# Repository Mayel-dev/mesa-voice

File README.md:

# Mesa Voice R1

Asistente de voz de sobremesa con botón para hablar, micrófono PDM, Wi-Fi, altavoz de 8 Ω y alimentación USB-C. Se conecta a un servidor Python local con faster-whisper, Ollama y Piper. El modo mock devuelve un tono para comprobar el transporte.

**Estado: entrega digital para un primer prototipo experimental, aún no construido.** La portadora pasa ERC y DRC con paridad esquema/PCB, sin conexiones pendientes. El firmware completo compila y enlaza para ESP32-S3; el backend pasa 41 pruebas y una petición HTTP real en localhost. Los tres STL son mallas cerradas y pasan la comprobación de interferencias nominales modeladas. No se ejecutó inferencia con modelos reales ni se probaron componentes físicos. Leer el [informe de validación](docs/validation.md) antes de fabricar.

## Entregables

| Carpeta / archivo | Contenido |
|---|---|
| `hardware/mesa-voice.kicad_pro` | Proyecto KiCad 9.0.6, esquema y PCB portadora propia de 64×54 mm, dos capas |
| `hardware/wiring.kicad_pro`, `wiring.kicad_sch` | Proyecto independiente de cableados del botón, LED y altavoz; seis conexiones verificadas |
| `hardware/Mesa.pretty`, bibliotecas `.kicad_sym` | Huellas y símbolos locales incluidos |
| `hardware/fabrication/` | Gerber X2, perforación PTH/NPTH, mapas, IPC-2581 y manifiesto con hashes |
| `hardware/mesa-voice-r1-fabrication.zip` | Paquete de fabricación generado sólo después de pasar comprobaciones |
| `hardware/previews/` | Vistas SVG y PNG del esquema, cobre y montaje |
| `hardware/references/` | Esquemas de los módulos de fabricante y atribución |
| `mechanical/` | CAD paramétrico OpenSCAD, tres STL y vistas de inspección |
| `firmware/` | Código ESP32-S3, configuración PlatformIO y pruebas C++ del protocolo |
| `backend/` | Servidor Python ejecutable, adaptadores locales y tests |
| `BOM.csv` | Lista consolidada con cantidades, referencias y especificaciones |
| `docs/` | Arquitectura, ensamblaje, mecánica, firmware, protocolo y validación |
| `validation/` | Informes originales, logs y plantilla para pruebas físicas |
| `tools/` | Generadores y verificaciones reproducibles |

La placa integra mediante zócalos un **Seeed XIAO ESP32S3 Sense 113991115** y un **Adafruit MAX98357A 3006**. Es una portadora personalizada, no un rediseño de sus circuitos RF/USB/MEMS internos. Usa cámara retirada y expansión Sense conectada. Caja cerrada 94×82×42 mm. No tiene wake word ni cancelación de eco.

## Probar el servidor sin hardware ni modelos

Python 3.12; desde `backend/`:

```powershell
python -m venv .venv
.\.venv\Scripts\Activate.ps1
python -m pip install -r requirements-dev.txt
python -m pytest -q
$env:MESA_TOKEN = (python -c "import secrets; print(secrets.token_hex(24))")
$env:MESA_MODE = 'mock'
python -m uvicorn mesa_voice.app:create_app --factory --host 127.0.0.1 --port 8000 --workers 1 --no-access-log
```

En otra terminal con el mismo token: `python -m scripts.smoke_client --output reply.wav`. Para una prueba autocontenida que inicia y detiene un servidor temporal, desde la raíz y con esas dependencias: `python tools/check_transport.py`. Sólo usa localhost y un token efímero.

Para modelos reales seguir [backend/README.md](backend/README.md). No se incluyen pesos, voces, credenciales ni descargas implícitas de modelos durante consultas. Para conectar el ESP32 configurar IP del PC y token en `firmware/include/secrets.h`; consultar [docs/firmware.md](docs/firmware.md). HTTP es adecuado únicamente para esta LAN de confianza; no publicar el servicio.

## Reproducir archivos técnicos

Abrir directamente el proyecto KiCad y el archivo OpenSCAD es suficiente para editarlos. Los generadores necesitan Python de KiCad con `pcbnew` y NumPy; no sirve un `pip install pcbnew` cualquiera. En Windows, KiCad 9 incluye `bin/python.exe`.

```powershell
# Desde la raíz del repositorio, con rutas adaptadas a la instalación:
& 'C:/Program Files/KiCad/9.0/bin/python.exe' tools/generate_hardware.py
python tools/generate_wiring.py
python tools/make_bom.py
python tools/release_hardware.py --kicad-cli 'C:/Program Files/KiCad/9.0/bin/kicad-cli.exe'
& 'C:/Program Files/KiCad/9.0/bin/python.exe' tools/check_interfaces.py
python -m pip install trimesh==4.6.8 numpy==2.2.6
python mechanical/export.py --openscad 'C:/Program Files/OpenSCAD/openscad.exe' --render
```

`generate_hardware.py` regenera esquema y PCB y reemplaza ediciones manuales; elegir editar fuente o CAD y conservar esa decisión. `generate_wiring.py` debe ejecutarse después, pues agrega la biblioteca de cableado. El trazado es determinista en geometría; los UUID y fechas de archivos KiCad pueden cambiar. El manifiesto corresponde a los archivos concretos incluidos, no a una promesa de igualdad binaria entre regeneraciones.

Para validar el firmware: `pip install platformio==6.1.18` y `python tools/build_firmware.py`. En Windows usar una ruta corta de caché con `--core-dir C:/ruta/corta/pio`. Las credenciales de esa compilación son ficticias y públicas; para tu dispositivo configurar y compilar el entorno `mesa_voice` como indica [firmware.md](docs/firmware.md). Plataforma, framework y toolchain están fijados. `.github/workflows/check.yml` prepara verificación en Ubuntu, **pero no se publicó ni ejecutó un workflow remoto**. El test C++ de host sí se compiló y ejecutó localmente.

El ZIP de fuentes omite cachés, entornos virtuales, credenciales y binarios de terceros. Incluye el código y la evidencia de compilación con hashes; el firmware de uso se genera con tu SSID y token. `tools/package_release.py` comprueba la vigencia de los informes y crea el ZIP y su SHA256. Consultar [reproducibilidad](docs/reproducibility.md) para los comandos completos.

## Fabricar y ensamblar

Seguir [docs/assembly.md](docs/assembly.md), [docs/mechanical.md](docs/mechanical.md) y la BOM. Hacer una revisión 1:1 de huellas contra los módulos recibidos antes de fabricar la primera placa. No se realizó ninguna compra ni se envió nada a fabricantes.

Los datos eléctricos de diseño, fuentes y riesgos están en [arquitectura](docs/architecture.md), [fuentes](docs/sources.md) e [informe de validación](docs/validation.md). El siguiente paso es preparar el servidor y sus modelos, configurar las credenciales del firmware y montar una unidad para completar la tabla de aceptación física. Esta revisión usa pulsar para hablar; no incluye activación por palabra.

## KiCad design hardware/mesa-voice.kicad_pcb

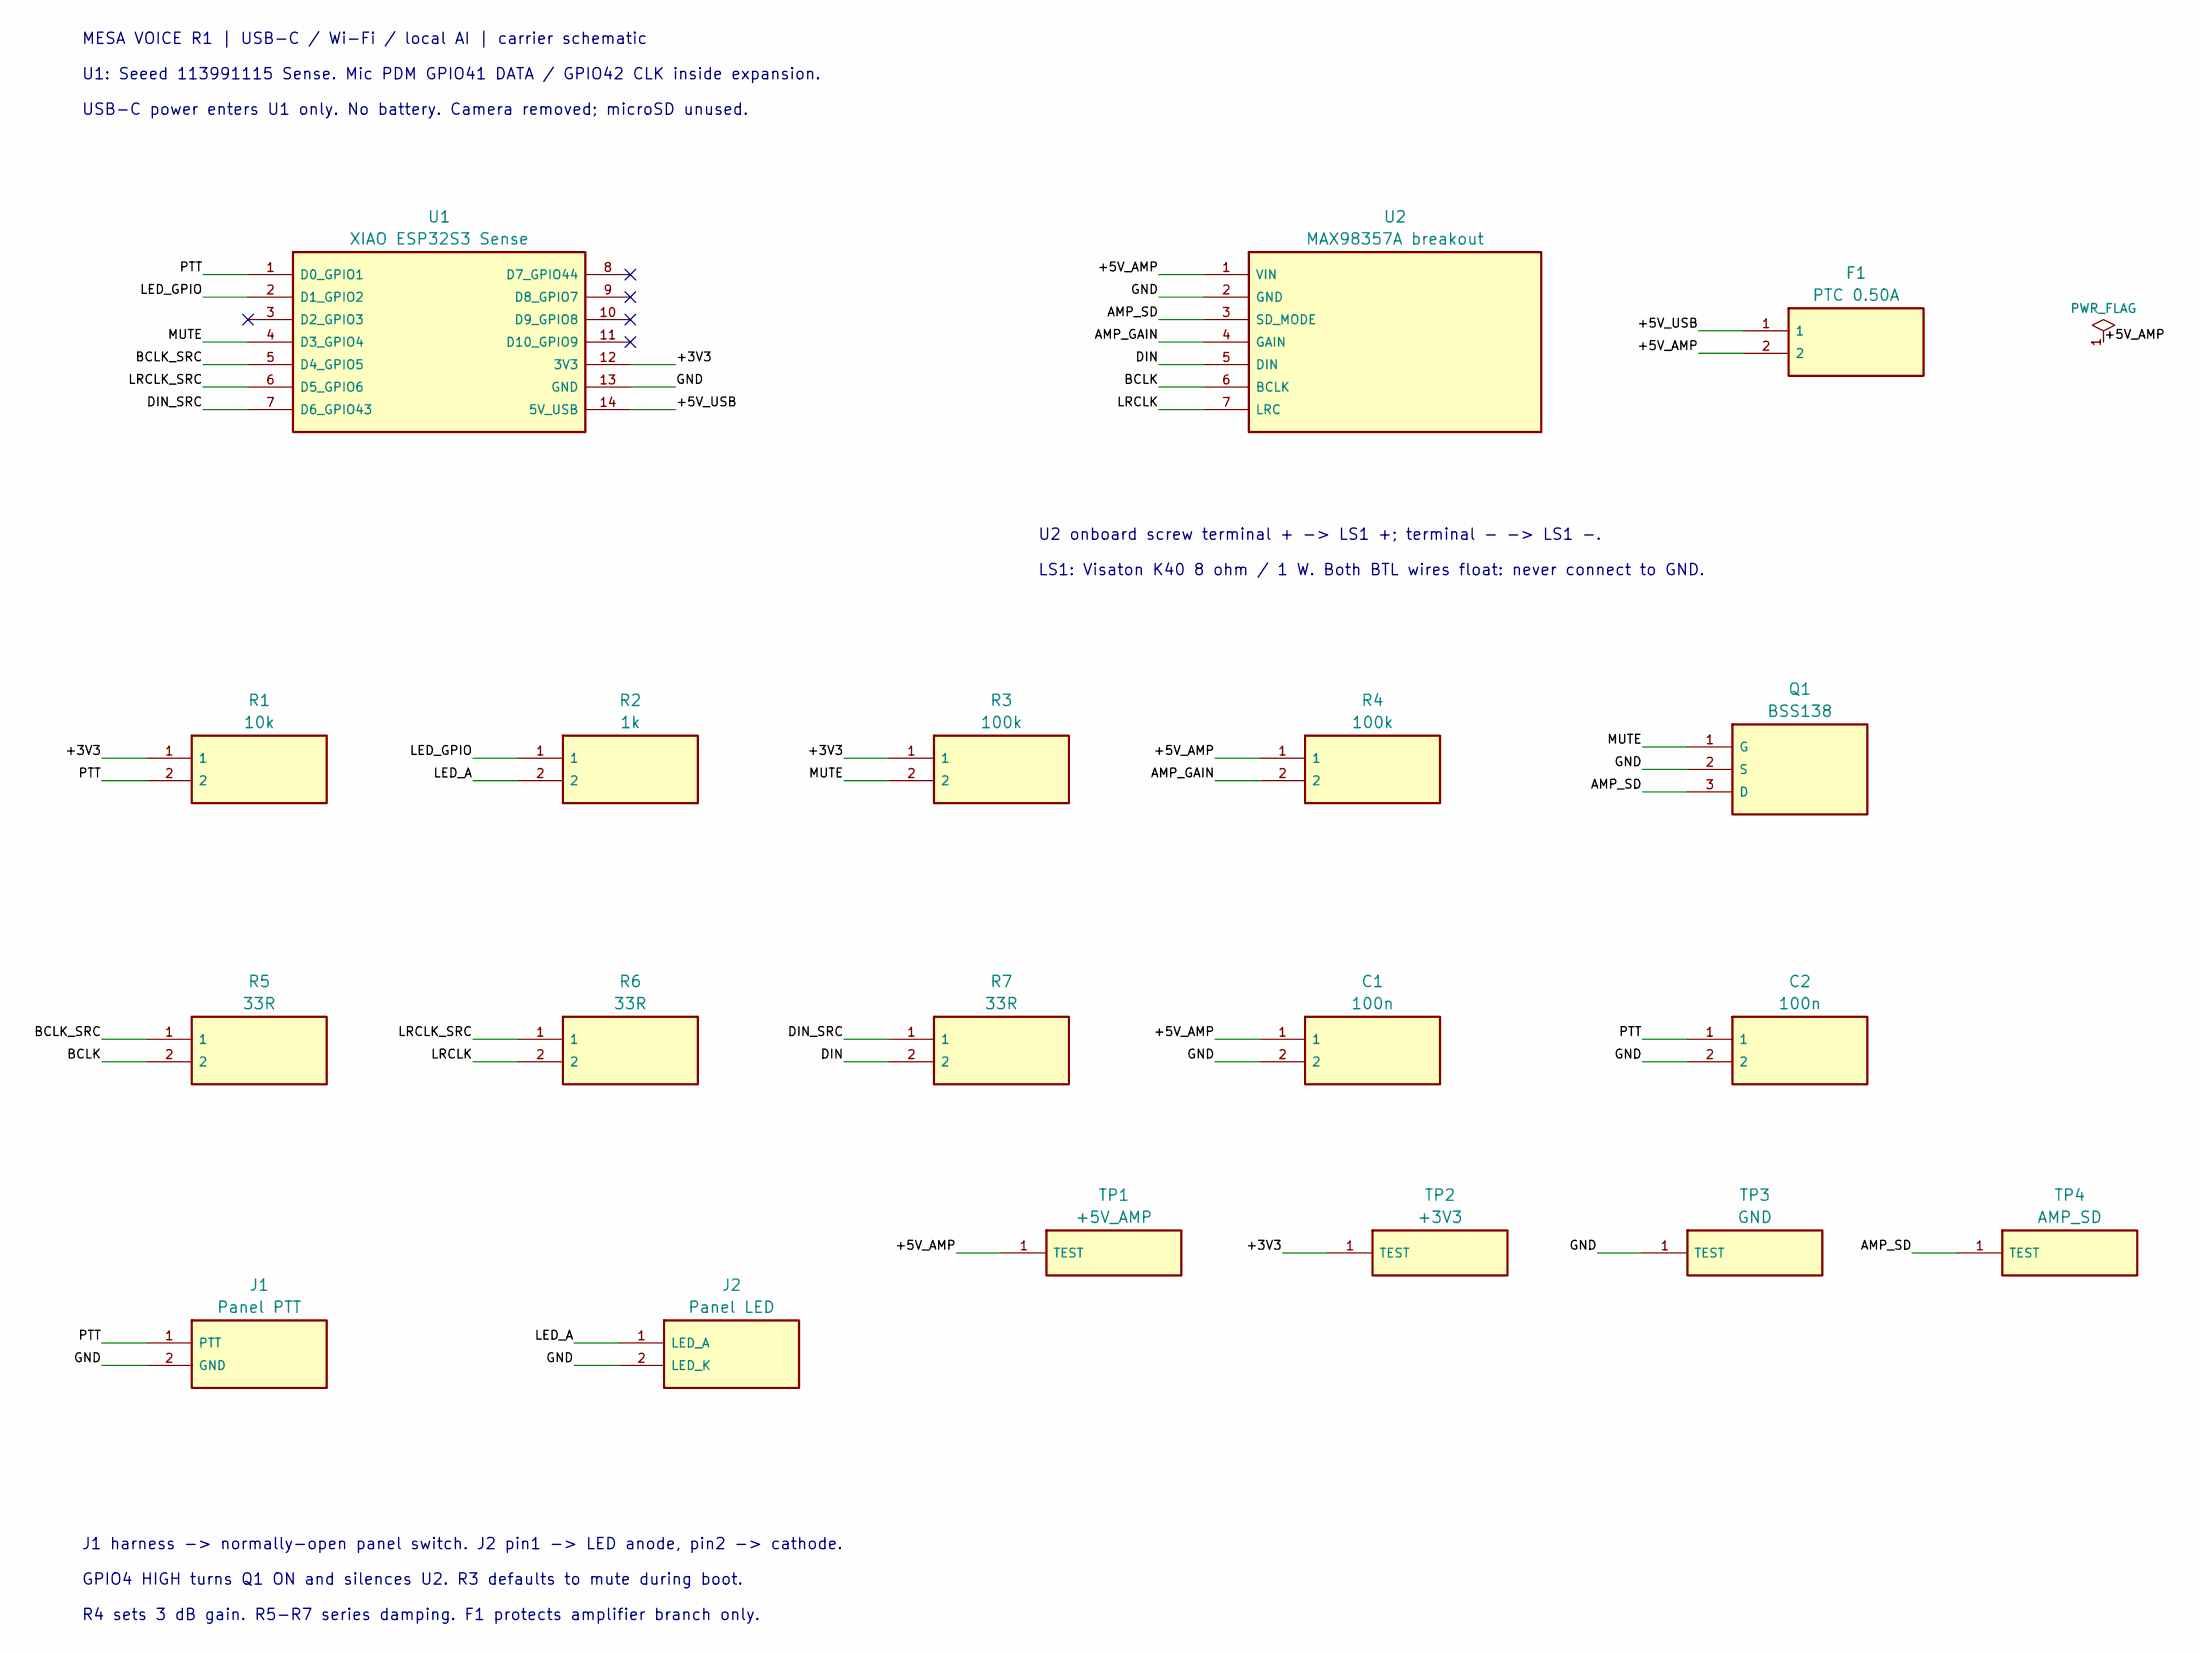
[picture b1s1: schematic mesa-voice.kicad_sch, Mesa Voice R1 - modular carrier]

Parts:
C1: 100n; C1; MPN Murata GRM21BR71C104KA01L
C2: 100n; C2; MPN Murata GRM21BR71C104KA01L
F1: PTC 0.50A; F1; MPN Bourns MF-MSMF050-2
J1: Panel PTT; J1; MPN JST B2B-XH-A(LF)(SN)
J2: Panel LED; J2; MPN JST B2B-XH-A(LF)(SN)
Q1: BSS138; Q1; MPN onsemi BSS138LT1G
R1: 10k; R1; MPN Yageo RC0805FR-0710KL
R2: 1k; R2; MPN Yageo RC0805FR-071KL
R3: 100k; R3; MPN Yageo RC0805FR-07100KL
R4: 100k; R4; MPN Yageo RC0805FR-07100KL
R5: 33R; R5; MPN Yageo RC0805FR-0733RL
R6: 33R; R6; MPN Yageo RC0805FR-0733RL
R7: 33R; R7; MPN Yageo RC0805FR-0733RL
TP1: +5V_AMP; TP1; MPN PCB test pad
TP2: +3V3; TP2; MPN PCB test pad
TP3: GND; TP3; MPN PCB test pad
TP4: AMP_SD; TP4; MPN PCB test pad
U1: XIAO ESP32S3 Sense; U1; MPN Seeed 113991115
U2: MAX98357A breakout; U2; MPN Adafruit 3006

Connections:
/+3V3: R1.1, R3.1, TP2.1, U1.12 (3V3)
/+5V_AMP: C1.1, F1.2, R4.1, TP1.1, U2.1 (VIN)
/+5V_USB: F1.1, U1.14 (5V_USB)
/AMP_GAIN: R4.2, U2.4 (GAIN)
/AMP_SD: Q1.3 (D), TP4.1, U2.3 (SD_MODE)
/BCLK: R5.2, U2.6 (BCLK)
/BCLK_SRC: R5.1, U1.5 (D4_GPIO5)
/DIN: R7.2, U2.5 (DIN)
/DIN_SRC: R7.1, U1.7 (D6_GPIO43)
/GND: C1.2, C2.2, J1.2 (GND), J2.2 (LED_K), Q1.2 (S), TP3.1, U1.13 (GND), U2.2 (GND)
/LED_A: J2.1 (LED_A), R2.2
/LED_GPIO: R2.1, U1.2 (D1_GPIO2)
/LRCLK: R6.2, U2.7 (LRC)
/LRCLK_SRC: R6.1, U1.6 (D5_GPIO6)
/MUTE: Q1.1 (G), R3.2, U1.4 (D3_GPIO4)
/PTT: C2.1, J1.1 (PTT), R1.2, U1.1 (D0_GPIO1)

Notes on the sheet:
MESA VOICE R1 | USB-C / Wi-Fi / local AI | carrier schematic
U1: Seeed 113991115 Sense. Mic PDM GPIO41 DATA / GPIO42 CLK inside expansion.
USB-C power enters U1 only. No battery. Camera removed; microSD unused.
U2 onboard screw terminal + -> LS1 +; terminal - -> LS1 -.
LS1: Visaton K40 8 ohm / 1 W. Both BTL wires float: never connect to GND.
J1 harness -> normally-open panel switch. J2 pin1 -> LED anode, pin2 -> cathode.
GPIO4 HIGH turns Q1 ON and silences U2. R3 defaults to mute during boot.
R4 sets 3 dB gain. R5-R7 series damping. F1 protects amplifier branch only.

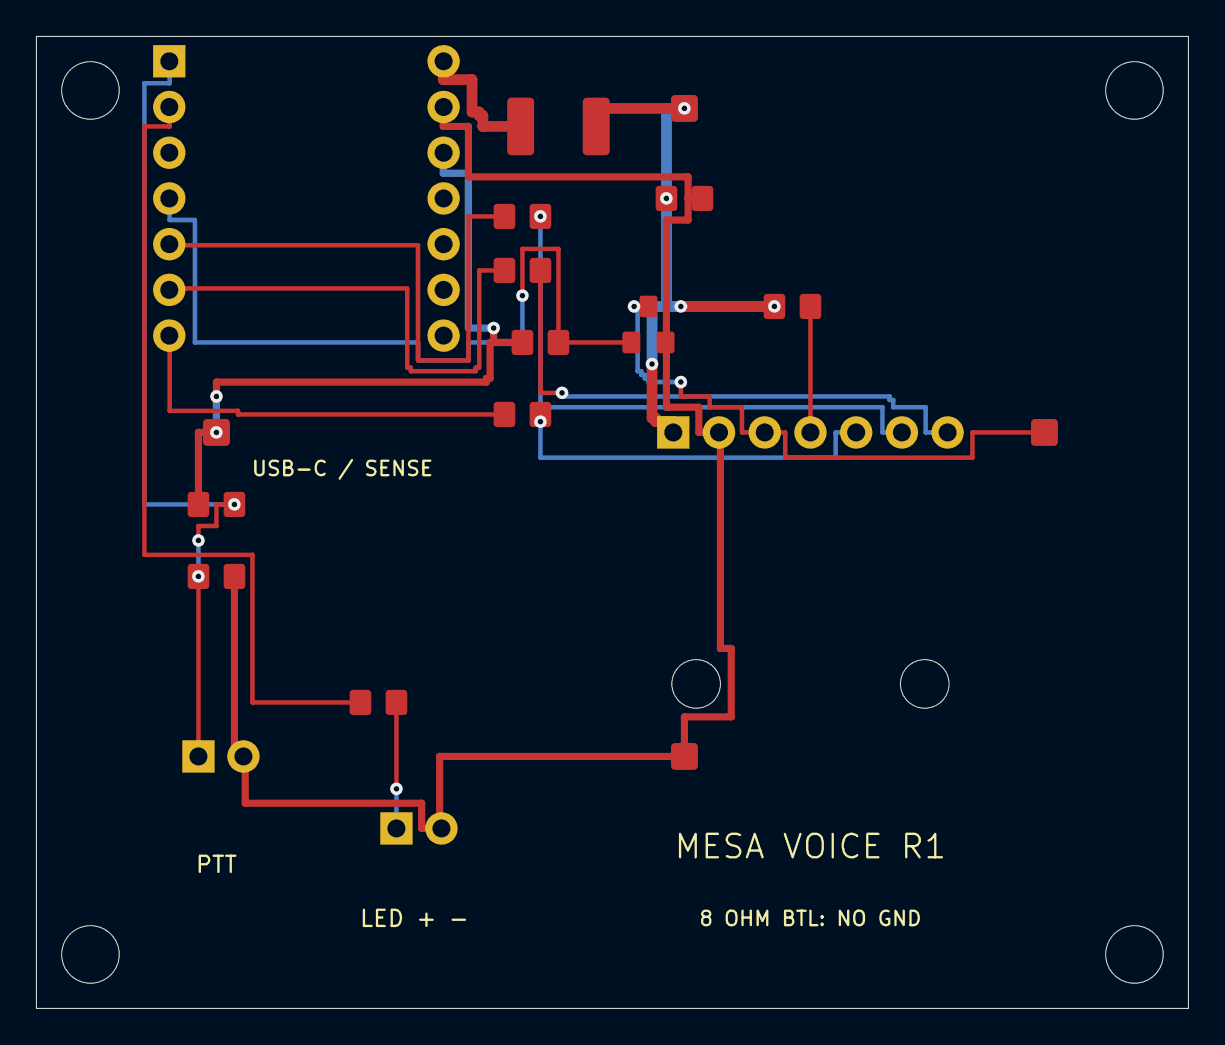
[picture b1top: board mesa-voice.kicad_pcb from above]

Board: 2 copper layers, 64.0 x 54.0 mm, 23 parts (0 on the bottom side), 16 nets.

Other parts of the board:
H1: M3; H1
H2: M3; H2
H3: M3; H3
H4: M3; H4

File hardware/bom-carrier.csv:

Reference,Value,Quantity,MPN,Footprint,Description
U1,XIAO ESP32S3 Sense,1,Seeed 113991115,Mesa:U1,"Includes USB-C, regulator, PSRAM, PDM microphone expansion; remove camera"
U2,MAX98357A breakout,1,Adafruit 3006,Mesa:U2,BTL screw terminals directly wired to LS1; 7-pin female socket
R1,10k,1,Yageo RC0805FR-0710KL,Mesa:R1,0805 resistor 1%
R2,1k,1,Yageo RC0805FR-071KL,Mesa:R2,0805 resistor 1%
R3,100k,1,Yageo RC0805FR-07100KL,Mesa:R3,0805 resistor 1%
R4,100k,1,Yageo RC0805FR-07100KL,Mesa:R4,0805 resistor 1%
R5,33R,1,Yageo RC0805FR-0733RL,Mesa:R5,0805 resistor 1%
R6,33R,1,Yageo RC0805FR-0733RL,Mesa:R6,0805 resistor 1%
R7,33R,1,Yageo RC0805FR-0733RL,Mesa:R7,0805 resistor 1%
Q1,BSS138,1,onsemi BSS138LT1G,Mesa:Q1,SOT-23 open drain; HIGH GPIO4 mutes amplifier
F1,PTC 0.50A,1,Bourns MF-MSMF050-2,Mesa:F1,"Resettable fuse only in amplifier branch, 1812 style 1 manufacturer land pattern"
C1,100n,1,Murata GRM21BR71C104KA01L,Mesa:C1,"0805 X7R 16V; C2 debounce, C1 local bypass"
C2,100n,1,Murata GRM21BR71C104KA01L,Mesa:C2,"0805 X7R 16V; C2 debounce, C1 local bypass"
J1,Panel PTT,1,JST B2B-XH-A(LF)(SN),Mesa:J1,"2-pin JST-XH 2.50mm vertical, keyed harness"
J2,Panel LED,1,JST B2B-XH-A(LF)(SN),Mesa:J2,"2-pin JST-XH 2.50mm vertical, keyed harness"
TP1,+5V_AMP,1,PCB test pad,Mesa:TP1,1.5 mm exposed test point
TP2,+3V3,1,PCB test pad,Mesa:TP2,1.5 mm exposed test point
TP3,GND,1,PCB test pad,Mesa:TP3,1.5 mm exposed test point
TP4,AMP_SD,1,PCB test pad,Mesa:TP4,1.5 mm exposed test point
H1,M3,1,M3 clearance,Mesa:H1,Non-plated mounting hole; M3 screw head max diameter 5.5mm
H2,M3,1,M3 clearance,Mesa:H2,Non-plated mounting hole; M3 screw head max diameter 5.5mm
H3,M3,1,M3 clearance,Mesa:H3,Non-plated mounting hole; M3 screw head max diameter 5.5mm
H4,M3,1,M3 clearance,Mesa:H4,Non-plated mounting hole; M3 screw head max diameter 5.5mm

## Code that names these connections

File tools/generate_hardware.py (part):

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right=['D7_GPIO44','D8_GPIO7','D9_GPIO8','D10_GPIO9','3V3','GND','5V_USB']
for i,n in enumerate(left): xp.append(pad(i+1,-7.62,-7.62+2.54*i,name=n,typ='bidirectional'))
for i,n in enumerate(right): xp.append(pad(i+8,7.62,7.62-2.54*i,name=n,typ='power_out' if i in (4,6) else 'passive' if i==5 else 'bidirectional'))
comp('U1','XIAO ESP32S3 Sense',(15,9),(58,52),xp,{1:'PTT',2:'LED_GPIO',4:'MUTE',5:'BCLK_SRC',6:'LRCLK_SRC',7:'DIN_SRC',12:'+3V3',13:'GND',14:'+5V_USB'},(-8.9,-10.5,8.9,10.5),'Seeed 113991115','Includes USB-C, regulator, PSRAM, PDM microphone expansion; remove camera')
# Amp header north edge; module body extends towards +Y. Correct order is
# VIN,GND,SD,GAIN,DIN,BCLK,LRC from left to right when terminal block is south.
anames=['VIN','GND','SD_MODE','GAIN','DIN','BCLK','LRC']
ap=[pad(i+1,-7.62+2.54*i,0,name=n,typ='power_in' if i==0 else 'input' if i in (2,4,5,6) else 'passive') for i,n in enumerate(anames)]
comp('U2','MAX98357A breakout',(43,22),(166,52),ap,{1:'+5V_AMP',2:'GND',3:'AMP_SD',4:'AMP_GAIN',5:'DIN',6:'BCLK',7:'LRCLK'},(-9.7,-2.54,9.7,15.3),'Adafruit 3006','BTL screw terminals directly wired to LS1; 7-pin female socket')

def r(ref,val,x,y,sx,sy,n1,n2,mpn):
    return comp(ref,val,(x,y),(sx,sy),[pad(1,-1,0,1.2,1.4,0),pad(2,1,0,1.2,1.4,0)],{1:n1,2:n2},(-1.8,-1,1.8,1),mpn,'0805 resistor 1%')
r('R1','10k',10,26,38,100,'+3V3','PTT','Yageo RC0805FR-0710KL')
r('R2','1k',19,37,80,100,'LED_GPIO','LED_A','Yageo RC0805FR-071KL')
r('R3','100k',28,17,122,100,'+3V3','MUTE','Yageo RC0805FR-07100KL')
r('R4','100k',42,15,164,100,'+5V_AMP','AMP_GAIN','Yageo RC0805FR-07100KL')
r('R5','33R',27,10,38,132,'BCLK_SRC','BCLK','Yageo RC0805FR-0733RL')
r('R6','33R',27,13,80,132,'LRCLK_SRC','LRCLK','Yageo RC0805FR-0733RL')
r('R7','33R',27,21,122,132,'DIN_SRC','DIN','Yageo RC0805FR-0733RL')
comp('Q1','BSS138',(34,16),(212,100),[pad(1,-.95,1,1.0,1.2,0,'G','input'),pad(2,.95,1,1.0,1.2,0,'S'),pad(3,0,-1,1.0,1.2,0,'D')],{1:'MUTE',2:'GND',3:'AMP_SD'},(-1.6,-1.7,1.6,1.7),'onsemi BSS138LT1G','SOT-23 open drain; HIGH GPIO4 mutes amplifier')
comp('F1','PTC 0.50A',(29,5),(218,52),[pad(1,-2.1,0,1.5,3.2,0),pad(2,2.1,0,1.5,3.2,0)],{1:'+5V_USB',2:'+5V_AMP'},(-3.2,-2,3.2,2),'Bourns MF-MSMF050-2','Resettable fuse only in amplifier branch, 1812 style 1 manufacturer land pattern')
for ref,x,y,sx,sy,n,val,mpn in [('C1',36,9,164,132,'+5V_AMP','100n','Murata GRM21BR71C104KA01L'),('C2',10,30,212,132,'PTT','100n','Murata GRM21BR71C104KA01L')]:
    comp(ref,val,(x,y),(sx,sy),[pad(1,-1,0,1.2,1.4,0),pad(2,1,0,1.2,1.4,0)],{1:n,2:'GND'},(-1.8,-1,1.8,1),mpn,'0805 X7R 16V; C2 debounce, C1 local bypass')
for ref,x,y,sx,sy,names,nets,mpn in [('J1',9,40,38,167,['PTT','GND'],{1:'PTT',2:'GND'},'JST B2B-XH-A(LF)(SN)'),('J2',20,44,92,167,['LED_A','LED_K'],{1:'LED_A',2:'GND'},'JST B2B-XH-A(LF)(SN)')]:
    comp(ref,'Panel '+('PTT' if ref=='J1' else 'LED'),(x,y),(sx,sy),[pad(1,0,0,1.8,1.8,1,name=names[0]),pad(2,2.5,0,1.8,1.8,1,name=names[1])],nets,(-2.5,-3,5,3),mpn,'2-pin JST-XH 2.50mm vertical, keyed harness')
for i,(x,y,n) in enumerate([(36,4,'+5V_AMP'),(10,22,'+3V3'),(36,40,'GND'),(56,22,'AMP_SD')],1):
    comp('TP'+str(i),n,(x,y),(135+(i-1)*36,155),[pad(1,0,0,1.5,1.5,0,name='TEST')],{1:n},(-1,-1,1,1),'PCB test pad','1.5 mm exposed test point')
for i,xy in enumerate([(3,3),(61,3),(3,51),(61,51)],1):
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    route_report.append(dict(net=net,start=a[:2],end=z[:2],segments=len(compact)-1))

# Route critical clocks first, ground last. Nearest spanning tree for fanout.
order=['GND','BCLK_SRC','LRCLK_SRC','DIN_SRC','BCLK','LRCLK','DIN','+5V_USB','+5V_AMP','AMP_GAIN','AMP_SD','MUTE','+3V3','LED_GPIO','LED_A','PTT']
for net in order:
    points=netpads[net][:]; done=[points.pop(0)]
    while points:
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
